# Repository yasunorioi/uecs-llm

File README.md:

# AgriHA (uecs-llm)

LLM による温室環境制御システム — 三層自律制御アーキテクチャ (v5移行中)

## アーキテクチャ

```mermaid
flowchart TD

subgraph group_group_runtime["Runtime stack"]
  node_node_mqtt["Mosquitto<br/>mqtt broker<br/>[mosquitto.conf]"]
end

subgraph group_group_control["Control layers"]
  node_node_emergency["Emergency guard<br/>safety cron<br/>[emergency_guard.sh]"]
  node_node_rule_engine["Rule engine<br/>deterministic control<br/>[rule_engine.py]"]
  node_node_rule_manager["Rule manager<br/>rules state<br/>[rule_manager.py]"]
  node_node_plan_executor["Plan executor<br/>action runner<br/>[plan_executor.py]"]
  node_node_rule_compiler["Rule compiler<br/>llm-assisted<br/>[rule_compiler.py]"]
  node_node_nullclaw(("NullClaw proxy<br/>llm gateway<br/>[nullclaw_proxy.py]"))
end

subgraph group_group_daemon["Hardware daemon"]
  node_node_daemon_main(("UniPi daemon<br/>[main.py]"))
  node_node_sensors["Sensors<br/>device inputs<br/>[sensor_loop.py]"]
  node_node_actuation["Actuators<br/>relay control<br/>[i2c_relay.py]"]
  node_node_rest_api["REST API<br/>http api<br/>[rest_api.py]"]
end

subgraph group_group_chat["UI and bot"]
  node_node_ui["Agriha UI<br/>web app<br/>[app.py]"]
  node_node_linebot["LINE bot<br/>chat handler<br/>[linebot_handler.py]"]
end

subgraph group_group_ml["Forecasting and offline ML"]
  node_node_forecast["Tide forecaster<br/>prediction<br/>[tide_forecaster.py]"]
  node_node_forecast_engine["Forecast engine<br/>ml integration<br/>[forecast_engine.py]"]
  node_node_dataset["Sensor data<br/>dataset<br/>[sensor_hourly.csv]"]
  node_node_tools["ML tools<br/>offline pipeline<br/>[train_tide.py]"]
end

subgraph group_group_ops["Deployment and config"]
  node_node_config["Runtime config<br/>yaml/conf<br/>[rules.yaml]"]
  node_node_systemd["Systemd units<br/>service orchestration"]
  node_node_setup["Install tools<br/>bootstrap<br/>[setup.sh]"]
end

node_node_sensors -->|"feeds"| node_node_daemon_main
node_node_daemon_main -->|"controls"| node_node_actuation
node_node_daemon_main -->|"serves"| node_node_rest_api
node_node_daemon_main -->|"publishes"| node_node_mqtt
node_node_mqtt -->|"events"| node_node_rule_engine
node_node_emergency -->|"forces safe state"| node_node_actuation
node_node_emergency -.->|"suppresses"| node_node_rule_engine
node_node_rule_engine -->|"loads rules"| node_node_rule_manager
node_node_rule_engine -->|"dispatches"| node_node_plan_executor
node_node_plan_executor -->|"issues actions"| node_node_rest_api
node_node_rule_compiler -->|"queries"| node_node_nullclaw
node_node_rule_compiler -->|"writes rules"| node_node_config
node_node_nullclaw -.->|"indirectly decouples"| node_node_mqtt
node_node_ui -->|"edits"| node_node_config
node_node_ui -->|"monitors"| node_node_daemon_main
node_node_linebot -->|"shares service"| node_node_ui
node_node_forecast -->|"runs in"| node_node_forecast_engine
node_node_tools -->|"trains on"| node_node_dataset
node_node_tools -->|"deploys"| node_node_forecast
node_node_systemd -->|"starts"| node_node_daemon_main
node_node_systemd -->|"starts"| node_node_ui
node_node_systemd -->|"starts"| node_node_nullclaw
node_node_systemd -->|"starts"| node_node_mqtt
node_node_setup -.->|"installs"| node_node_systemd
node_node_config -->|"configures"| node_node_emergency
node_node_config -->|"configures"| node_node_rule_engine
node_node_config -->|"guides"| node_node_rule_compiler
node_node_config -->|"backing store"| node_node_ui

click node_node_daemon_main "https://github.com/yasunorioi/uecs-llm/blob/v5/src/agriha/daemon/main.py"
click node_node_sensors "https://github.com/yasunorioi/uecs-llm/blob/v5/src/agriha/daemon/sensor_loop.py"
click node_node_actuation "https://github.com/yasunorioi/uecs-llm/blob/v5/src/agriha/daemon/i2c_relay.py"
click node_node_rest_api "https://github.com/yasunorioi/uecs-llm/blob/v5/src/agriha/daemon/rest_api.py"
click node_node_mqtt "https://github.com/yasunorioi/uecs-llm/blob/v5/docker/mosquitto/mosquitto.conf"
click node_node_emergency "https://github.com/yasunorioi/uecs-llm/blob/v5/src/agriha/control/emergency_guard.sh"
click node_node_rule_engine "https://github.com/yasunorioi/uecs-llm/blob/v5/src/agriha/control/rule_engine.py"
click node_node_rule_manager "https://github.com/yasunorioi/uecs-llm/blob/v5/src/agriha/control/rule_manager.py"
click node_node_plan_executor "https://github.com/yasunorioi/uecs-llm/blob/v5/src/agriha/control/plan_executor.py"
click node_node_rule_compiler "https://github.com/yasunorioi/uecs-llm/blob/v5/src/agriha/control/rule_compiler.py"
click node_node_nullclaw "https://github.com/yasunorioi/uecs-llm/blob/v5/src/agriha/control/nullclaw_proxy.py"
click node_node_ui "https://github.com/yasunorioi/uecs-llm/blob/v5/src/agriha/chat/app.py"
click node_node_linebot "https://github.com/yasunorioi/uecs-llm/blob/v5/src/agriha/chat/linebot_handler.py"
click node_node_forecast "https://github.com/yasunorioi/uecs-llm/blob/v5/src/agriha/control/tide_forecaster.py"
click node_node_forecast_engine "https://github.com/yasunorioi/uecs-llm/blob/v5/src/agriha/control/forecast_engine.py"
click node_node_dataset "https://github.com/yasunorioi/uecs-llm/blob/v5/data/sensor_hourly.csv"
click node_node_tools "https://github.com/yasunorioi/uecs-llm/blob/v5/tools/train_tide.py"
click node_node_config "https://github.com/yasunorioi/uecs-llm/blob/v5/config/rules.yaml"
click node_node_systemd "https://github.com/yasunorioi/uecs-llm/blob/v5/systemd/unipi-daemon.service"
click node_node_setup "https://github.com/yasunorioi/uecs-llm/blob/v5/setup.sh"

classDef toneNeutral fill:#f8fafc,stroke:#334155,stroke-width:1.5px,color:#0f172a
classDef toneBlue fill:#dbeafe,stroke:#2563eb,stroke-width:1.5px,color:#172554
classDef toneAmber fill:#fef3c7,stroke:#d97706,stroke-width:1.5px,color:#78350f
classDef toneMint fill:#dcfce7,stroke:#16a34a,stroke-width:1.5px,color:#14532d
classDef toneRose fill:#ffe4e6,stroke:#e11d48,stroke-width:1.5px,color:#881337
classDef toneIndigo fill:#e0e7ff,stroke:#4f46e5,stroke-width:1.5px,color:#312e81
classDef toneTeal fill:#ccfbf1,stroke:#0f766e,stroke-width:1.5px,color:#134e4a
class node_node_mqtt toneBlue
class node_node_emergency,node_node_rule_engine,node_node_rule_manager,node_node_plan_executor,node_node_rule_compiler,node_node_nullclaw toneAmber
class node_node_daemon_main,node_node_sensors,node_node_actuation,node_node_rest_api toneMint
class node_node_ui,node_node_linebot toneRose
class node_node_forecast,node_node_forecast_engine,node_node_dataset,node_node_tools toneIndigo
class node_node_config,node_node_systemd,node_node_setup toneTeal
```

## 設計原則

- **下層が上層を黙らせる**: Layer 1ロックアウト中はLayer 2/3は動作しない
- **各層独立動作**: 上層が死んでも下層の安全機構は生きる
- **RPi単一構成**: 全てRaspberry Pi上で完結（VPS不要・クラウドAPI不要）
- **オフラインファースト**: NullClaw Proxy でローカル完結。通信費ゼロ
- **HW不在でも起動**: I2Cデバイス未接続時はNullRelay（no-op）で全サービス起動継続
- **マルチLLM対応**: OpenAI SDK互換でClaude/GPT/Gemini/Ollama/NullClawを切替可能

## NullClaw（デフォルトLLMプロバイダー）

v5ではNullClaw Proxy (port 3001) をデフォルトLLMとして採用。
NullClaw CLIをOpenAI SDK互換エンドポイントとして公開するプロキシサーバー。

- **API**: OpenAI互換 `/v1/chat/completions` エンドポイント (port 3001)
- **tool calling**: 非対応（センサーデータをプロンプトに事前埋め込みで代替）
- **実装**: `src/agriha/control/nullclaw_proxy.py`
- **systemdサービス**: `agriha-nullclaw-proxy.service`

```
APIキーなし (デフォルト)     APIキーあり
      │                          │
      ▼                          ▼
  NullClaw直行              クラウドAPI試行
  (localhost:3001)               │
                           成功? ─┬─ Yes → クラウド応答
                                 └─ No  → NullClawフォールバック
```

## LINE Bot

RPi上のagriha-ui内で直接稼働（VPS不要）。Cloudflare TunnelまたはNginx+Let's Encryptで外部公開。

- LLMプロバイダーにはNullClaw Proxyを使用（tool calling非対応のためプロンプト埋め込み方式）

## ディレクトリ構成

| パッケージ | 場所 | 説明 |
|-----------|------|------|
| `agriha.control` | `src/agriha/control/` | 三層制御（emergency_guard, rule_engine, rule_compiler, forecast_engine[v4], plan_executor[v4]） |
| `agriha.daemon` | `src/agriha/daemon/` | ハードウェアデーモン（I2C, GPIO, MQTT, REST API） |
| `agriha.chat` | `src/agriha/chat/` | ローカルWebUI（ダッシュボード+設定画面+LINE Bot） |
| `config` | `config/` | 設定テンプレート（rules.yaml, channel_map.yaml, forecast.yaml等） |

## セットアップ

### 前提条件

- Raspberry Pi 5 (8GB推奨)
- Raspberry Pi OS Bookworm (64-bit)
- Python 3.11+
- cmake, git

### 手順

```bash
# 1. Mosquitto (MQTT broker)
sudo apt install -y mosquitto mosquitto-clients

# 2. AgriHA セットアップ
git clone https://github.com/yasunorioi/uecs-llm.git ~/uecs-llm
cd ~/uecs-llm && git checkout v5
sudo bash setup.sh

# 3. I2C / 1-Wire 有効化
sudo raspi-config nonint do_i2c 0
sudo raspi-config nonint do_onewire 0

# 4. WireGuard VPN設定（setup.shでテンプレート配置済み）
sudo nano /etc/wireguard/wg0.conf   # キー・IP設定を編集
sudo systemctl enable --now wg-quick@wg0

# 5. 起動
sudo systemctl start agriha-nullclaw-proxy unipi-daemon agriha-ui
```

`sudo bash setup.sh` で以下が自動完了:
- Python venv作成 + パッケージインストール
- `/etc/agriha/` に設定ファイル配置
- `/var/lib/agriha/`, `/var/log/agriha/` ディレクトリ作成
- agriha システムユーザー作成 + 所有権設定
- systemd サービス有効化（unipi-daemon, agriha-ui, agriha-nullclaw-proxy）
- 三層制御 cron 設定
- WireGuard VPNインストール + テンプレート配置
- Nginx設定配置（LINE Bot外部公開用）

### DS18B20 温度センサー設定（HW接続後）

```bash
# デバイスID確認
ls /sys/bus/w1/devices/
# → 28-xxxxxxxxxxxx 形式のIDが表示される

# 設定ファイルに追記
sudo nano /etc/agriha/unipi_daemon.yaml
# onewire:
#   devices:
#     - "28-xxxxxxxxxxxx"

sudo systemctl restart unipi-daemon
```

### 動作確認

```bash
# 全サービスの状態確認
for svc in agriha-nullclaw-proxy unipi-daemon agriha-ui mosquitto; do
  echo "$svc: $(systemctl is-active $svc)"
done

# NullClaw API確認
curl -s http://localhost:3001/v1/models | python3 -m json.tool

# Web UI確認 (デフォルト認証: admin/agriha)
curl -s -u admin:agriha http://localhost:8501/

# メモリ確認
free -h
```

## Web UI ログイン

| 項目 | デフォルト値 | 環境変数 |
|------|:----------:|----------|
| ユーザー名 | `admin` | `UI_AUTH_USER` |
| パスワード | `agriha` | `UI_AUTH_PASS` |

HTTP Basic認証。変更は `/opt/agriha/.env` に記載するか、systemd の `Environment=` で指定。

```bash
# .env で変更する例
echo 'UI_AUTH_USER=myuser' >> /opt/agriha/.env
echo 'UI_AUTH_PASS=mypassword' >> /opt/agriha/.env
sudo systemctl restart agriha-ui
```

## systemd サービス一覧

| サービス | ポート | 説明 |
|---------|:------:|------|
| `agriha-nullclaw-proxy.service` | 3001 | NullClaw OpenAI互換プロキシ |
| `unipi-daemon.service` | 8080 | センサー・リレー・MQTT・REST APIデーモン |
| `agriha-ui.service` | 8501 | Web UI + LINE Bot (FastAPI + htmx) |
| `mosquitto.service` | 1883 | MQTT broker |

```bash
# ログ確認
journalctl -u agriha-nullclaw-proxy -f
journalctl -u unipi-daemon -f
```

## cron (三層制御)

| ジョブ | 間隔 | 説明 |
|--------|------|------|
| emergency_guard.sh | 毎分 | Layer 1: 緊急制御 |
| rule_engine.py | 10分毎 | Layer 2: ルールベース制御 |
| tide_forecaster.py | 10分毎 | TiDE予測更新 (InAirTemp/InAirHumid/InAirCO2 6h先行予測) |
| rule_compiler.py review | 週次 月曜07:00 | Layer 3 (v5): ルール候補レビュー・自動更新 |
| distiller.py | 週次 月曜03:00 | ルール候補蒸留 |
| reflection.py | 週次 月曜07:00 | LINE反省会（⚠ ファイル削除済み・要修復） |
| forecast_engine.py | — | v4 legacy、コメントアウト（無効） |
| plan_executor.py | — | v4 legacy、コメントアウト（無効） |

## Web UI 設定画面

`http://<RPi-IP>:8501/settings` から以下を編集可能:

- **LLMプロバイダー**: NullClaw / Anthropic(Claude) / OpenAI / Gemini / Ollama 選択
- **APIキー設定**: NullClaw以外を選択した場合のみ必要
- **システムプロンプト**: Layer 3 LLMへの指示文
- **緊急閾値**: Layer 1 の高温/低温閾値
- **制御ルール**: Layer 2 の rules.yaml（YAML直接編集+構文チェック）
- **チャンネルマップ**: リレーチャンネル割当（channel_map.yaml）

## LLMプロバイダー切替

forecast_engine.py は OpenAI SDK 互換クライアントを使用。
設定画面のプルダウンから選択するか、`/etc/agriha/forecast.yaml` を直接編集。

| プロバイダー | base_url | APIキー | 備考 |
|-------------|----------|---------|------|
| NullClaw (デフォルト) | `http://localhost:3001/v1/` | 不要 | オフライン・無料・tool calling不可 |
| Anthropic (Claude) | `https://api.anthropic.com/v1/` | 必要 | 高精度・tool calling可 |
| OpenAI (GPT) | `https://api.openai.com/v1/` | 必要 | tool calling可 |
| Google (Gemini) | `https://generativelanguage.googleapis.com/v1beta/openai/` | 必要 | tool calling可 |
| Ollama (ローカル) | `http://localhost:11434/v1/` | 不要 | 要Ollama別途インストール |

## 設定ファイル

`/etc/agriha/` に配置される設定ファイル一覧:

| ファイル | 説明 |
|---------|------|
| `rules.yaml` | Layer 2 制御ルール |
| `channel_map.yaml` | リレーチャンネル割当 |
| `forecast.yaml` | LLMプロバイダー設定 |
| `thresholds.yaml` | 緊急閾値 |
| `emergency.conf` | Layer 1 緊急制御設定 |
| `agri_knowledge.yaml` | 農学知識ベース（rule_compiler用） |
| `crop_irrigation.yaml` | 作物別灌水設定 |
| `rule_candidates.yaml` | 蒸留ルール候補 |
| `system_prompt.txt` | LLMシステムプロンプト |
| `unipi_daemon.example.yaml` | デーモン設定テンプレート |
| `nginx.conf` | Nginx設定テンプレート |
| `wg0.conf.template` | WireGuard VPN設定テンプレート |

## スクリプト

| スクリプト | 説明 |
|-----------|------|
| `scripts/agriha-capture.sh` | 定時カメラキャプチャ（cron 5分） |
| `scripts/agriha-growth-archive.sh` | 生育ログアーカイブ |
| `scripts/setup-camera.sh` | カメラHWセットアップ |
| `scripts/start-tmux.sh` | 開発用tmuxセッション起動 |

## USB SIM / APN設定

固定回線のない圃場向けに、USB SIMモデムによるモバイル回線接続をサポート。

- setup.sh実行時にUSBモデムを自動検出し、ModemManager + NetworkManagerを設定
- APN設定はプリセットから選択: **SORACOM** (デフォルト) / IIJmio / 手動入力

## テスト

```bash
pip install -e ".[dev]"
pytest tests/ -v
```

## 依存インストール

```bash
# 通常（daemon + TiDE予測）
pip install -e ".[daemon,tide]"

# RPi4/5 (aarch64): tflite-runtime が自動選択される
# x86_64 開発環境: tensorflow にフォールバック

# TiDE関連（numpy + tflite-runtime/tensorflow）
pip install -e ".[tide]"
```

> **RPi4補足**: `tflite-runtime` は `tensorflow` 全体より軽量（~50MB vs ~500MB）。
> setup.sh は自動で `[daemon,tide]` をインストールする。

## ライセンス

MIT

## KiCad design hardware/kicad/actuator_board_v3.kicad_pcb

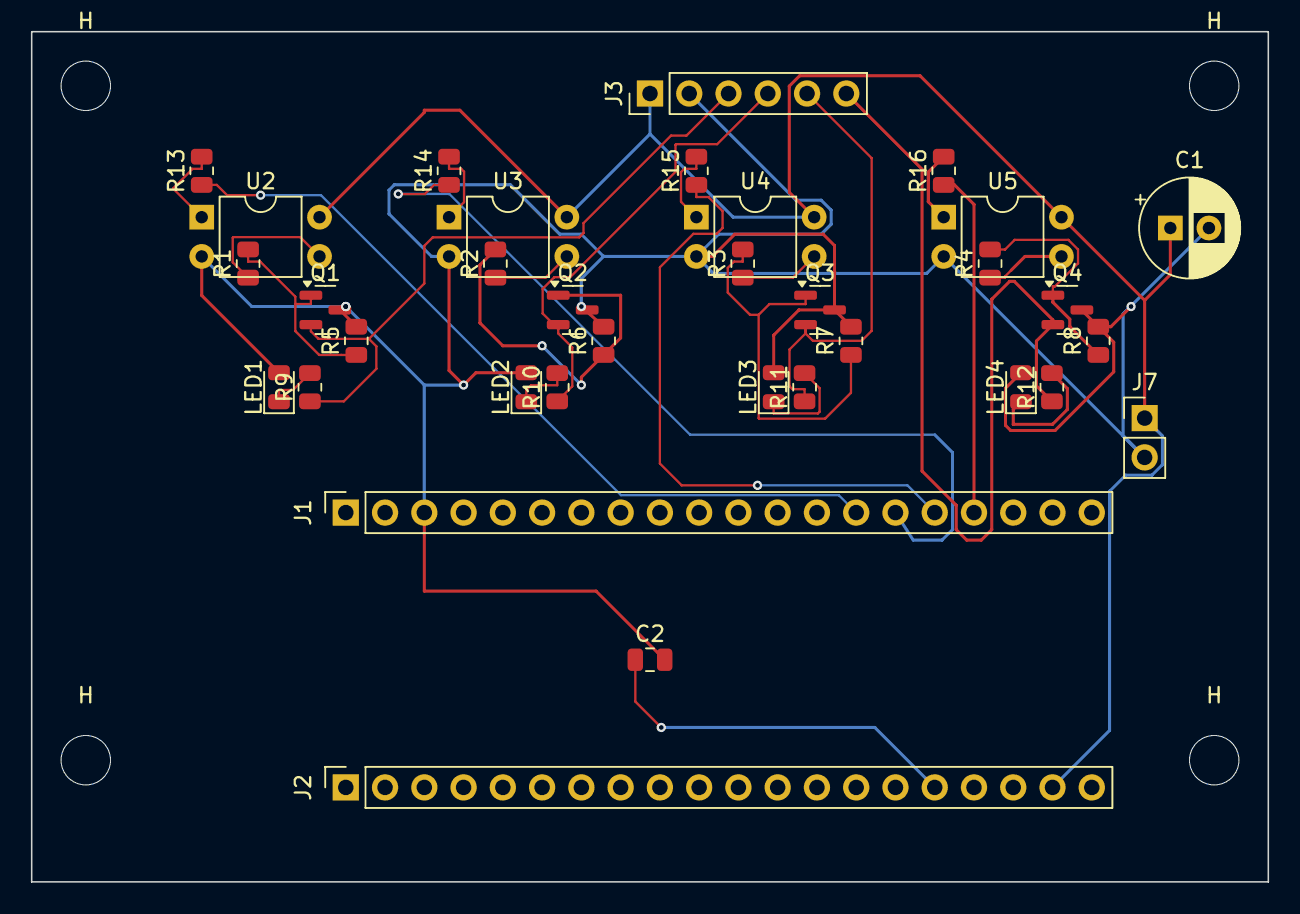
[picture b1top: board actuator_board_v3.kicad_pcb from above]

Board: 2 copper layers, 80.0 x 55.0 mm, 38 parts (0 on the bottom side), 27 nets.

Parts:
C1: 100u; CP_Radial_D6.3mm_P2.50mm
C2: 100n; C_0805_2012Metric
H: MountingHole_3.2mm_M3
H#2, H#3, H#4: MountingHole_3.2mm_M3
J1: Pico_Left; PinSocket_1x20_P2.54mm_Vertical
J2: Pico_Right; PinSocket_1x20_P2.54mm_Vertical
J3: RELAY_MOD; PinHeader_1x06_P2.54mm_Vertical
J7: 5V_EXT; PinHeader_1x02_P2.54mm_Vertical
LED1, LED2, LED3, LED4: Red; LED_0805_2012Metric
Q1, Q2, Q3, Q4: 2N7002; SOT-23
R1, R2, R3, R4: 100; R_0805_2012Metric
R5, R6, R7, R8: 10k; R_0805_2012Metric
R9, R10, R11, R12, R13, R14, R15, R16: 330; R_0805_2012Metric
U2, U3, U4, U5: PC817; DIP-4_W7.62mm

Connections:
unnamed: C1.1, J2.19, J3.1, J7.1, U2.4, U3.4, U4.4, U5.4
unnamed: C1.2, C2.2, J1.3, J3.2, J7.2, LED1.2, LED2.2, LED3.2, LED4.2, Q1.3, Q2.3, Q3.3, Q4.3, R5.2, R6.2, R7.2, R8.2, U2.2, U3.2, U4.2, U5.2
unnamed: J1.14, R13.1
unnamed: J1.15, R14.1
unnamed: J1.16, R15.1
unnamed: J1.17, R16.1
unnamed: C2.1, J2.16
unnamed: LED1.1, R9.2
unnamed: LED2.1, R10.2
unnamed: LED3.1, R11.2
unnamed: LED4.1, R12.2
unnamed: J3.3, Q1.2, R9.1
unnamed: Q1.1, R1.2, R5.1
unnamed: J3.4, Q2.2, R10.1
unnamed: Q2.1, R2.2, R6.1
unnamed: J3.5, Q3.2, R11.1
unnamed: Q3.1, R3.2, R7.1
unnamed: J3.6, Q4.2, R12.1
unnamed: Q4.1, R4.2, R8.1
unnamed: R1.1, U2.3
unnamed: R2.1, U3.3
unnamed: R3.1, U4.3
unnamed: R4.1, U5.3
unnamed: R13.2, U2.1
unnamed: R14.2, U3.1
unnamed: R15.2, U4.1
unnamed: R16.2, U5.1

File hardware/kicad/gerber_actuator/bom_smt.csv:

Comment,Designator,Footprint,LCSC
100n,C2,C_0805_2012Metric,C49678
Red,"LED1,LED2,LED3,LED4",LED_0805_2012Metric,C84256
2N7002,"Q1,Q2,Q3,Q4",SOT-23,C8545
330,"R9,R10,R11,R12,R13,R14,R15,R16",R_0805_2012Metric,C17630
100,"R1,R2,R3,R4",R_0805_2012Metric,C17408
10k,"R5,R6,R7,R8",R_0805_2012Metric,C17414

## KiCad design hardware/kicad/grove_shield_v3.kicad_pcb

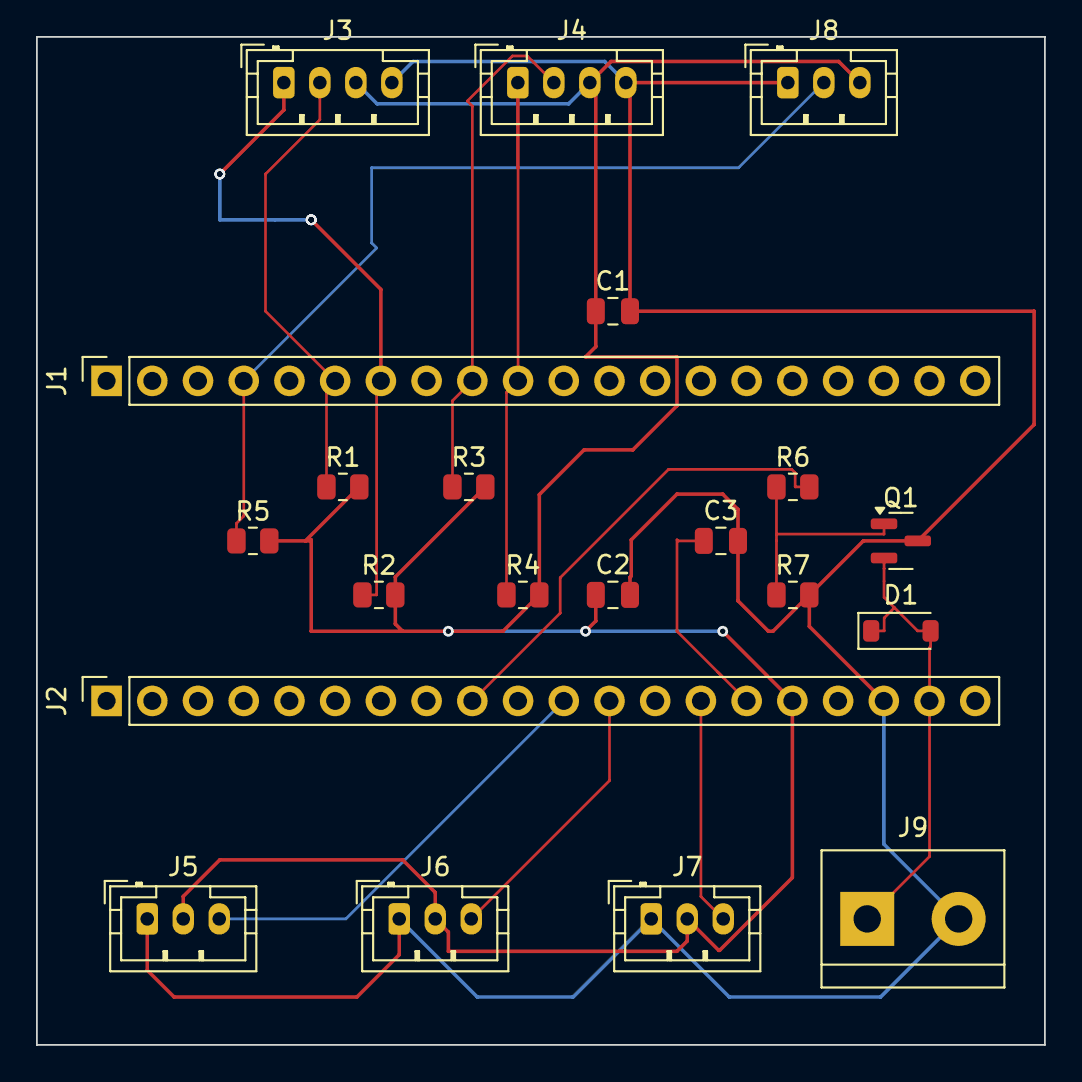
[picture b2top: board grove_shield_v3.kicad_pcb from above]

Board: 2 copper layers, 56.0 x 56.0 mm, 21 parts (0 on the bottom side), 14 nets.

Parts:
C1, C2, C3: 100n; C_0805_2012Metric
D1: 1N4148; D_SOD-123
J1: Pico_Left; PinSocket_1x20_P2.54mm_Vertical
J2: Pico_Right; PinSocket_1x20_P2.54mm_Vertical
J3: Grove_I2C0; JST_PH_B4B-PH-K_1x04_P2.00mm_Vertical
J4: Grove_I2C1; JST_PH_B4B-PH-K_1x04_P2.00mm_Vertical
J5: ADC0; JST_PH_B3B-PH-K_1x03_P2.00mm_Vertical
J6: ADC1; JST_PH_B3B-PH-K_1x03_P2.00mm_Vertical
J7: ADC2; JST_PH_B3B-PH-K_1x03_P2.00mm_Vertical
J8: 1-Wire; JST_PH_B3B-PH-K_1x03_P2.00mm_Vertical
J9: Fan; TerminalBlock_bornier-2_P5.08mm
Q1: 2N7002; SOT-23
R1, R2, R3, R4, R5: 4.7k; R_0805_2012Metric
R6: 100; R_0805_2012Metric
R7: 10k; R_0805_2012Metric

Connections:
unnamed: D1.1, D1.2, J2.19, J9.1, Q1.2
unnamed: J1.4, J8.2, R5.1
unnamed: J1.6, J3.2, R1.1
unnamed: J1.7, J3.1, R2.1
unnamed: J1.9, J4.2, R3.1
unnamed: J1.10, J4.1, R4.1
unnamed: J2.9, R6.2
unnamed: J2.11, J5.3
unnamed: J2.12, J6.3
unnamed: J2.14, J7.3
unnamed: C3.1, J2.15
unnamed: C1.1, C2.1, J2.16, J3.3, J4.3, J5.2, J6.2, J7.2, J8.3, R1.2, R2.2, R3.2, R4.2, R5.2
unnamed: C1.2, C2.2, C3.2, J2.18, J3.4, J4.4, J5.1, J6.1, J7.1, J8.1, J9.2, Q1.3, R7.2
unnamed: Q1.1, R6.1, R7.1

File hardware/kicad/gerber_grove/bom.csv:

Comment,Designator,Footprint,LCSC
100n,"C1,C2,C3",C_0805_2012Metric,C49678
1N4148,D1,D_SOD-123,C81598
Pico_Left,J1,PinSocket_1x20_P2.54mm_Vertical,
Pico_Right,J2,PinSocket_1x20_P2.54mm_Vertical,
Grove_I2C0,J3,JST_PH_B4B-PH-K_1x04_P2.00mm_Vertical,
Grove_I2C1,J4,JST_PH_B4B-PH-K_1x04_P2.00mm_Vertical,
ADC0,J5,JST_PH_B3B-PH-K_1x03_P2.00mm_Vertical,
ADC1,J6,JST_PH_B3B-PH-K_1x03_P2.00mm_Vertical,
ADC2,J7,JST_PH_B3B-PH-K_1x03_P2.00mm_Vertical,
1-Wire,J8,JST_PH_B3B-PH-K_1x03_P2.00mm_Vertical,
Fan,J9,TerminalBlock_bornier-2_P5.08mm,
2N7002,Q1,SOT-23,C8545
4.7k,"R1,R2,R3,R4,R5",R_0805_2012Metric,C17673
100,R6,R_0805_2012Metric,C17408
10k,R7,R_0805_2012Metric,C17414

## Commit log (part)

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2026-03-01 feat: Layer 1 emergency_guard.sh + bats tests (cmd_286)
    - src/v2_control/emergency_guard.sh: POSIX sh互換 緊急停止スクリプト
    - layer1.env読み込み (AGRIHA_CONFIG/LOCKOUT/LOGで上書き可)
    - Step1a: Layer 1自身のロックアウト確認 (lockout_state.json)
    - Step1b: CommandGate ロックアウト確認 (GET /api/status)
    - Step2: センサーデータ取得 (GET /api/sensors)
    - Step3: CCM InAirTemp優先、Misolフォールバック
2026-03-01 feat: agriha_ui backend - FastAPI routes + config (cmd_287)
    - src/agriha_ui/app.py (~210行): FastAPI + Jinja2 + Basic Auth
    - GET / → dashboard.html (sensors/lockout/rule_engine/forecast/relays)
    - GET /api/dashboard-partial → htmx部分更新用
    - GET /settings → settings.html (thresholds + system_prompt編集)
    - POST /settings/prompt → system_prompt.txt保存 (バックアップ付き)
    - POST /settings/thresholds → thresholds.yaml保存 (バリデーション付き)
2026-03-01 chore: remove old architecture files + archive design doc (cmd_288)
2026-03-01 docs: add v2 pending files - design doc + control loop update + prompt fix (cmd_288)
2026-03-01 docs: README.md v2 architecture rewrite (cmd_288)
2026-03-01 fix: remove old architecture references from linebot + start-tmux (cmd_288)
2026-03-01 fix: rename check_ollama_health → check_llm_health in linebot/app.py (cmd_288)
2026-03-01 docs: README.md setup section + fix hardcoded paths in agriha_ui (cmd_289)
2026-03-01 fix: setup.sh service path + remove old services/ dir (cmd_289 rework)
2026-03-03 fix: is_layer1_locked() now引数追加でテスト修復 (cmd_298)
2026-03-04 docs: 設計書v3.5 反省会モード+Starlink監視+カメラ (cmd_299)
2026-03-04 docs: 設計書§7蒸留パイプライン追記 (cmd_300)
2026-03-04 test: 層間連携テスト5件(lockout/rain/wind/鮮度/複合) §3.4準拠
2026-03-04 feat: rule_manager.py(候補承認/却下/30日腐敗/rules.yaml昇格)+rule_candidates.yaml初期化
2026-03-04 fix: audit_108指摘修正(cron .venvパス+generate_candidates id付与)
2026-03-04 feat: reflection.py反省会コア(候補選定+質問生成+回答処理+reflection_memoテーブル)+config/reflection.yaml
    - config/reflection.yaml: weekly/月曜07:00/max_items=3/nag=2週/downgrade=4週
    - src/agriha/control/reflection.py: load_config/select_candidates/generate_question/
    create_reflection_memos/process_answer/check_nag_status/run_reflection
    - forecast_engine.py init_db(): reflection_memoテーブル追加
    - systemd/agriha-cron: 反省会cron追加 (月曜07:00, 蒸留4時間後)
    - tests/control/test_reflection.py: 16件 402/402 PASS
2026-03-04 fix: systemdパス__REPO_DIR__化+setup.sh sed置換+.env.example VC API KEY追加
2026-03-04 fix: setup.sh VENV_DIR venv→.venv修正 (audit_113)
2026-03-04 fix: /opt/agriha配置対応(setup.sh手順+README+cron+log dir)
2026-03-04 fix: setup.sh chown+enable完結化+README 3ステップ圧縮(農家UX)
2026-03-04 fix: pyproject.toml依存漏れ全修正(jinja2/python-multipart/astral)
2026-03-04 fix: pyproject.tomlにanthropic>=0.20追加(遅延import漏れ, audit_116)
2026-03-04 feat: カメラセットアップ分離(setup-camera.sh新規+agriha-cronカメラ削除)
2026-03-06 feat: NullClawデフォルト化 Phase2 — nullclaw_proxy.py+フォールバック実装 (cmd_334/subtask_765)
2026-03-06 docs: agriha_v4_spec.md NullClawデフォルト化反映 (§3.3/§5.1/§5.6)
2026-03-06 fix: forecast_engine api_key変数名衝突修正 — unipi用api_key/LLM用llm_api_keyに分離 (audit指摘)
2026-03-06 fix: agriha-nullclaw-proxy.service venv→システムuvicorn+WorkingDirectory追加 (RPi実機対応)
2026-03-06 fix: save系関数のrename→write_text上書きに変更 — /etc配下ディレクトリ権限エラー修正 (cmd_336)
2026-03-06 feat: LINE Bot LLM→NullClawFallbackClient切替+set_relay制御不可案内 (cmd_337/subtask_769)
2026-04-25 docs: add architecture diagram (Mermaid) to README
